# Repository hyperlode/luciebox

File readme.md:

# About
A busy box is the official word for a sensory exploratory platform for babies. 
This project was made as a birth day gift for Lucie Ameije 2019-04
Turns out, it's as interesting to adults as it is to babies. 
95% ignores abandos the box after five minutes. 5% gets hooked for days. 

Made by Uncle Sensory Overlode.
www.ameije.com

PCB and code:
https://github.com/hyperlode/luciebox

Manual:
https://docs.google.com/document/d/10EQDtFDWs3Xm5eaC9KIhdYMh6ftuR9I12zDFt4Ep7Ls/edit?usp=sharing

# Upload
- Open the arduino IDE
- Open the "luciebox" folder in the IDE
- Compile and upload should go smoothly.
- (alternatively Platformio for VS-code can be used)

# Versions
- F301: 2021-03-19: Version uploaded before sending boxes home
- F302: 2021-04-20 For the v3 startburst pcb. 
-F303: 2021-04-21: Small bugfixes, easier debug of selector dial in settings app . 
-F306: 2021-10-15: Improve user experience. Dream mode app better suited for toddlers.

# Manual
- A manual is in the "documentation folder"
- The most up to date manual is a google docs. Online at https://docs.google.com/document/d/1WturQFRmZjFw0ZYRagNDqMO8tlJvhG8SyK8Gmxv2Aj4/edit#

# Motto
- There are no bugs, only features.  Or: every bug is a feature.  (it doesn't matter if things work or not).

# Making off:
- pcbs ordered 20191112   jlc pcb (jlcpcb.com) 10 pieces for about 30cad.
- Invoice No：2818290A20191113144921
- Invoice Date：13/11/2019
- Batch No：W201911131447210

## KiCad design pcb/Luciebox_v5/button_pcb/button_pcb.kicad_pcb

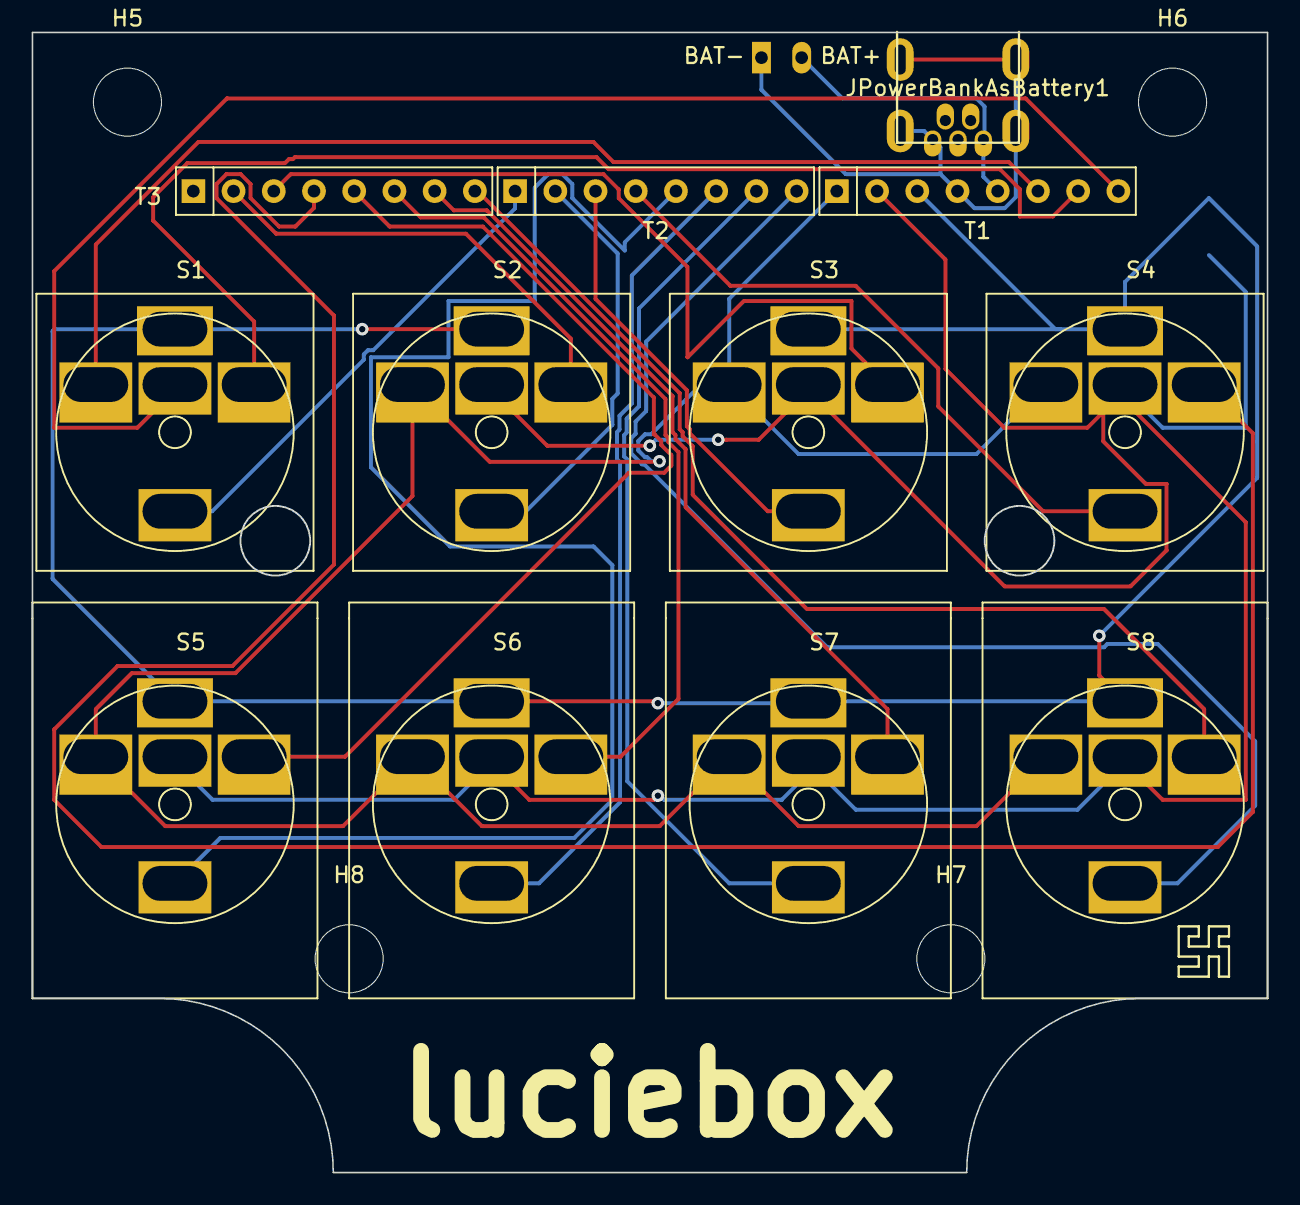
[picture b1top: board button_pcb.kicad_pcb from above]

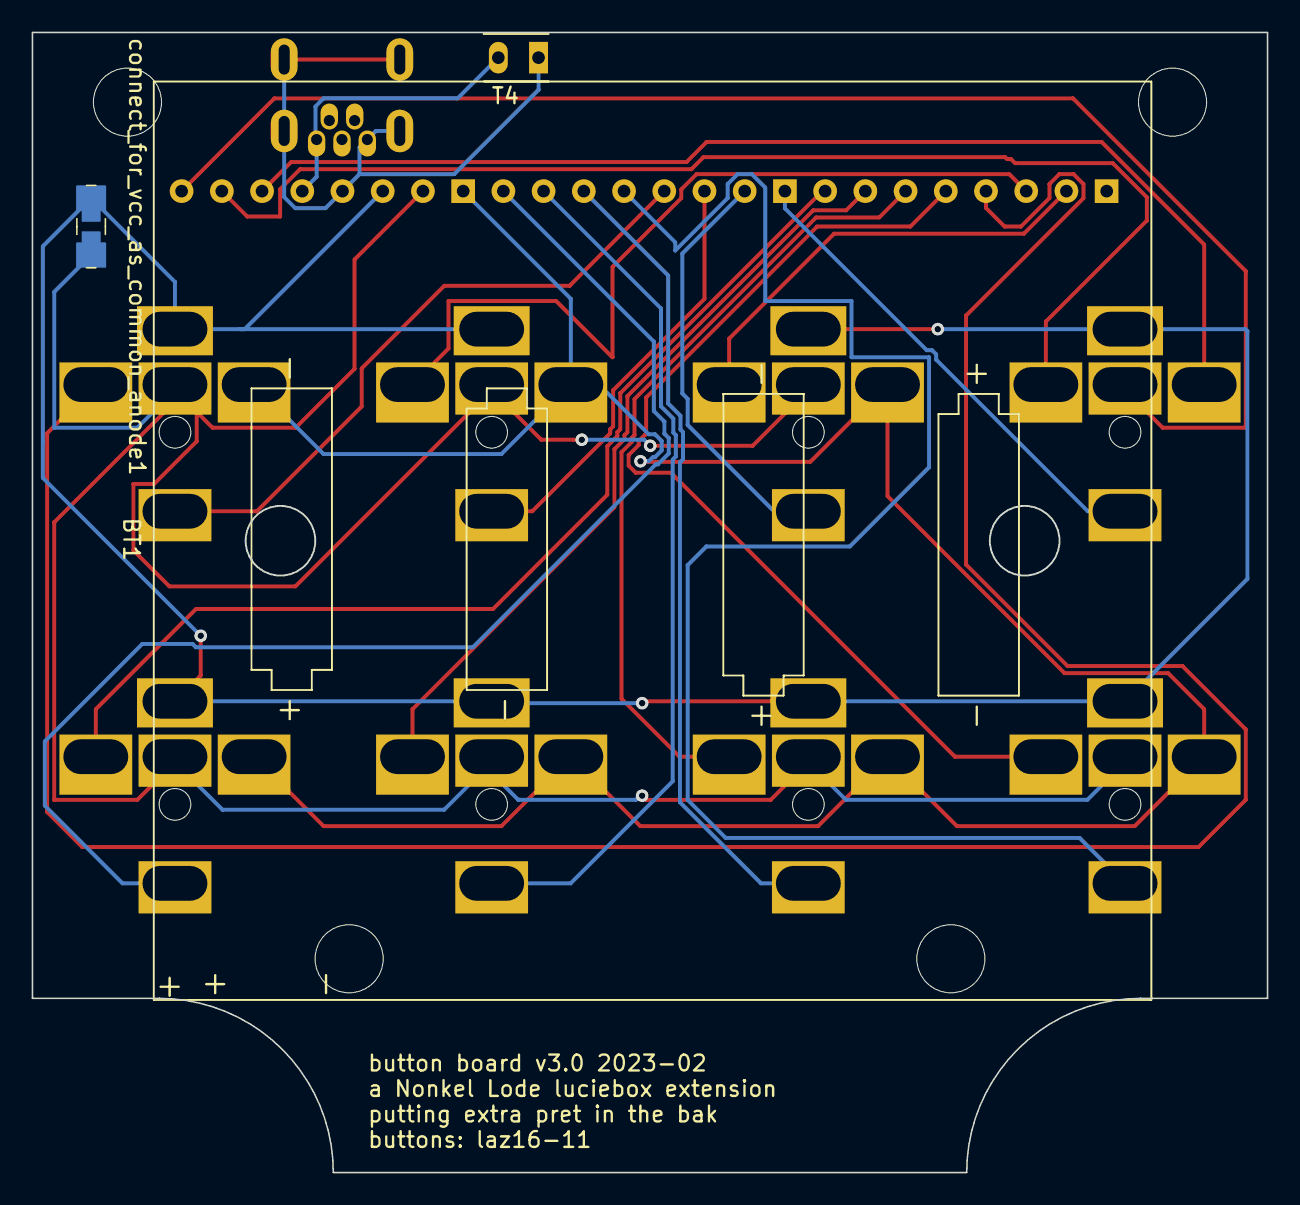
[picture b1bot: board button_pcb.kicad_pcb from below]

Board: 2 copper layers, 78.0 x 72.0 mm, 19 parts (3 on the bottom side), 23 nets.

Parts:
BT1: 4xAA_Battery_holder; BatteryHolder_4xAA
H5, H6, H7, H8: MountingHole; MountingHole_4.3mm_M4
JPowerBankAsBattery1: USB_B_Mini; usb_mini_Molex-0548190519
S1, S2, S3, S4: button_laz16-11; button_square_17.5x17.5mm_big_holes
S5, S6, S7, S8: button_laz16-11; button_LAZ16-11_big_holes
T1, T2, T3: terminal_8x1; Terminal_8x1_100mil
T4: terminal_2x1; Terminal_2x1_100mil
connect_for_vcc_as_common_anode1: R_Small; 1206_0805

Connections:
/common Anode: S1.4 (LED_+), S2.4 (LED_+), S3.4 (LED_+), S4.4 (LED_+), S5.4 (LED_+), S6.4 (LED_+), S7.4 (LED_+), S8.4 (LED_+), T1.3, connect_for_vcc_as_common_anode1.2
GND: S2.2 (NC), S3.2 (NC), S4.2 (NC), S5.2 (NC), S6.2 (NC), S7.2 (NC), S8.2 (NC), T1.1
unnamed: JPowerBankAsBattery1.5 (VBUS), T1.5, T4.2
unnamed: JPowerBankAsBattery1.1 (GND), JPowerBankAsBattery1.6 (Shield), T1.4, T4.1
unnamed: S1.1 (NO), T1.8
unnamed: S1.2 (NC), T1.6
unnamed: S1.3 (C), T1.7
unnamed: S1.5 (LED_-), T2.1
unnamed: S2.3 (C), T3.2
unnamed: S2.5 (LED_-), T2.2
unnamed: S3.3 (C), T3.3
unnamed: S3.5 (LED_-), T2.3
unnamed: S4.3 (C), T3.4
unnamed: S4.5 (LED_-), T2.4
unnamed: S5.3 (C), T3.5
unnamed: S5.5 (LED_-), T2.5
unnamed: S6.3 (C), T3.6
unnamed: S6.5 (LED_-), T2.6
unnamed: S7.3 (C), T3.7
unnamed: S7.5 (LED_-), T2.7
unnamed: S8.3 (C), T3.8
unnamed: S8.5 (LED_-), T2.8
VCC: S2.1 (NO), S3.1 (NO), S4.1 (NO), S5.1 (NO), S6.1 (NO), S7.1 (NO), S8.1 (NO), T1.2, connect_for_vcc_as_common_anode1.1

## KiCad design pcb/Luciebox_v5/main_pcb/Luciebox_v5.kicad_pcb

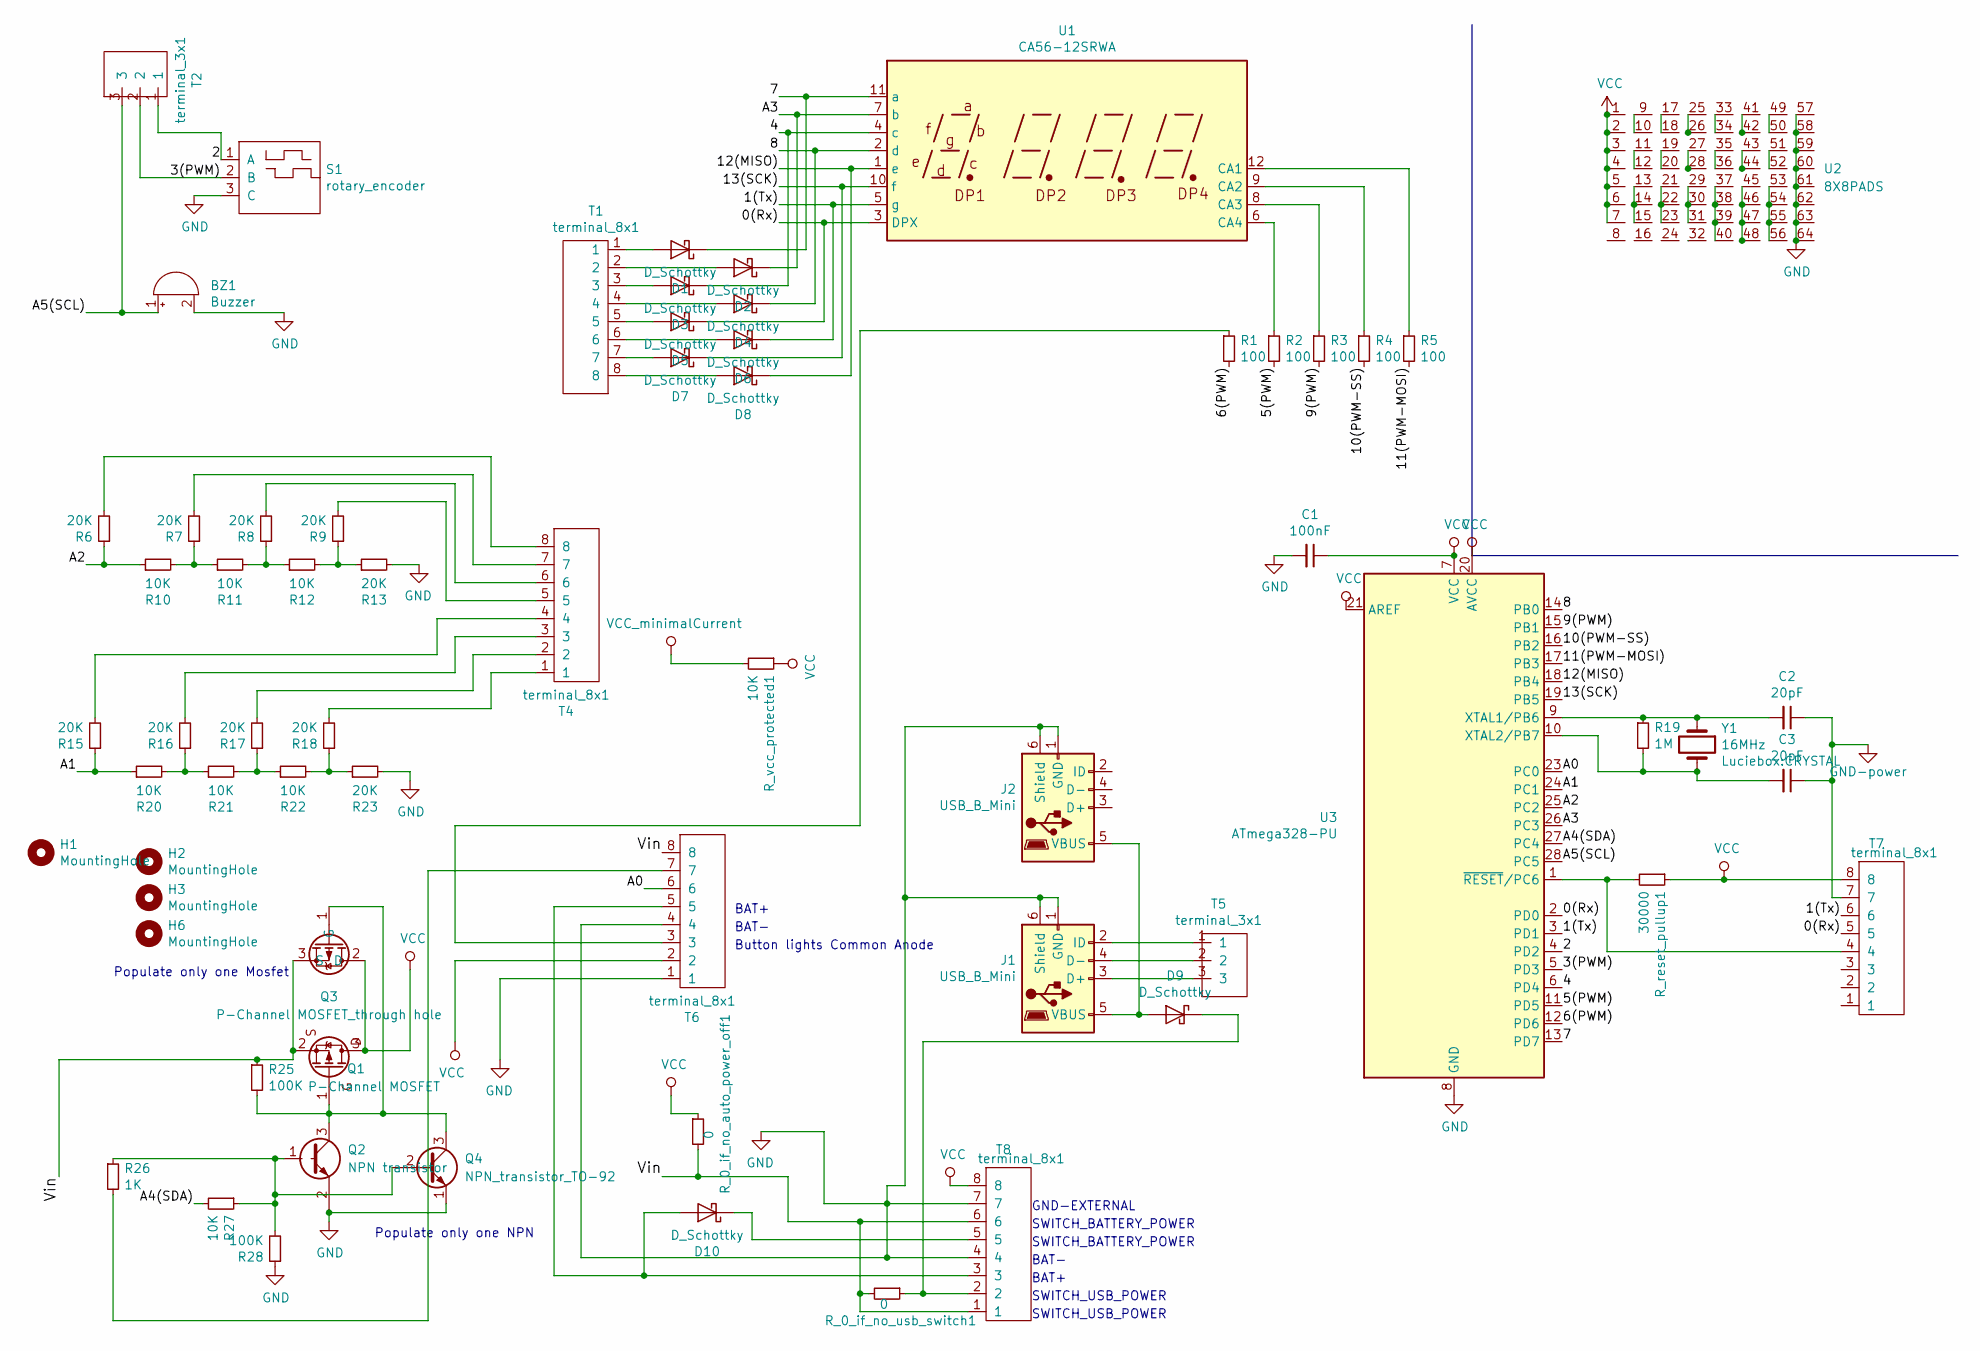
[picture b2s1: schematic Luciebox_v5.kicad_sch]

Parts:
BZ1: Buzzer; buzzer
C1: 100nF; 0603_1608Metric
C2, C3: 20pF; 0603_1608Metric
D1, D2, D3, D4, D5, D6, D7, D8, D9, D10: D_Schottky; D_SMA
H1, H2, H3, H6: MountingHole; MountingHole_4.3mm_M4
J1, J2: USB_B_Mini; usb_mini_Molex-0548190519
Q1: P-Channel MOSFET; SOT-23
Q2: NPN transistor; SOT-23
Q3: P-Channel MOSFET_through hole; TO-218-3_Vertical
Q4: NPN_transistor_TO-92; TO-92
R1, R2, R3, R4, R5: 100; 0603_1608Metric
R6, R7, R8, R9, R13, R15, R16, R17, R18, R23: 20K; 0603_1608Metric
R10, R11, R12, R20, R21, R22, R27: 10K; 0603_1608Metric
R19: 1M; 0603_1608Metric
R25, R28: 100K; 0603_1608Metric
R26: 1K; 0603_1608Metric
R_0_if_no_auto_power_off1, R_0_if_no_usb_switch1: 0; 0603_1608Metric
R_reset_pullup1: 30000; 0603_1608Metric
R_vcc_protected1: 10K; 0603_1608Metric
S1: rotary_encoder
T1, T4, T6, T7, T8: terminal_8x1; Terminal_8x1_100mil
T2, T5: terminal_3x1; Terminal_3x1_100mil
U1: CA56-12SRWA
U2: 8X8PADS; 8X8PADS_100mil
U3: ATmega328-PU; DIP-28_W7.62mm
Y1: 16MHz; CRYSTAL

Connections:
/0(Rx): D5.1 (K), T7.5, U1.3 (DPX), U3.2 (PD0)
/1(Tx): D6.1 (K), T7.6, U1.5 (g), U3.3 (PD1)
/2: S1.1 (A), T2.1, U3.4 (PD2)
/3(PWM): S1.2 (B), T2.2, U3.5 (PD3)
/4: D3.1 (K), U1.4 (c), U3.6 (PD4)
/5(PWM): R2.2, U3.11 (PD5)
/6(PWM): R1.2, U3.12 (PD6)
/7: D1.1 (K), U1.11 (a), U3.13 (PD7)
/8: D4.1 (K), U1.2 (d), U3.14 (PB0)
/9(PWM): R3.2, U3.15 (PB1)
/10(PWM-SS): R4.2, U3.16 (PB2)
/11(PWM-MOSI): R5.2, U3.17 (PB3)
/12(MISO): D8.1 (K), U1.1 (e), U3.18 (PB4)
/13(SCK): D7.1 (K), U1.10 (f), U3.19 (PB5)
/A0: T6.6, U3.23 (PC0)
/A1: R15.1, R20.1, U3.24 (PC1)
/A2: R6.1, R10.1, U3.25 (PC2)
/A3: D2.1 (K), U1.7 (b), U3.26 (PC3)
/A4(SDA): R27.2, U3.27 (PC4)
/A5(SCL): BZ1.1 (-), T2.3, U3.28 (PC5)
/Vin: Q1.2 (S), Q3.3 (S), R25.1, R_0_if_no_auto_power_off1.2, R_0_if_no_usb_switch1.2, T6.8, T8.1, T8.6
unnamed: C2.2, R19.1, U3.9 (XTAL1/PB6), Y1.1
unnamed: C3.2, R19.2, U3.10 (XTAL2/PB7), Y1.2
unnamed: D1.2 (A), T1.1
unnamed: D2.2 (A), T1.2
unnamed: D3.2 (A), T1.3
unnamed: D4.2 (A), T1.4
unnamed: D5.2 (A), T1.5
unnamed: D6.2 (A), T1.6
unnamed: D7.2 (A), T1.7
unnamed: D8.2 (A), T1.8
unnamed: D9.1 (K), R_0_if_no_usb_switch1.1, T8.2
unnamed: D9.2 (A), J1.5 (VBUS), J2.5 (VBUS)
unnamed: D10.1 (K), T8.5
unnamed: D10.2 (A), T6.5, T8.3
unnamed: J1.2 (ID), T5.1
unnamed: J1.3 (D+), T5.3
unnamed: J1.4 (D-), T5.2
unnamed: Q1.1 (G), Q2.3 (E), Q3.1 (G), Q4.3 (E), R25.2
unnamed: Q2.1 (C), Q4.2 (B), R26.1, R27.1, R28.2
unnamed: R1.1, T6.3
unnamed: R2.1, U1.6 (CA4)
unnamed: R3.1, U1.8 (CA3)
unnamed: R4.1, U1.9 (CA2)
unnamed: R5.1, U1.12 (CA1)
unnamed: R6.2, T4.8
unnamed: R7.2, T4.7
unnamed: R8.2, T4.6
unnamed: R9.2, T4.5
unnamed: R7.1, R10.2, R11.1
unnamed: R8.1, R11.2, R12.1
unnamed: R9.1, R12.2, R13.1
unnamed: R15.2, T4.4
unnamed: R16.1, R20.2, R21.1
unnamed: R16.2, T4.3
unnamed: R17.1, R21.2, R22.1
unnamed: R17.2, T4.2
unnamed: R18.1, R22.2, R23.1
unnamed: R18.2, T4.1
unnamed: R26.2, T6.7
unnamed: R_reset_pullup1.2, T7.4, U3.1 (~RESET/PC6)
unnamed: U2.9, U2.10
unnamed: U2.11, U2.12
unnamed: U2.13, U2.14, U2.15
unnamed: U2.17, U2.18
unnamed: U2.19, U2.20
unnamed: U2.21, U2.22, U2.23
unnamed: U2.25, U2.26
unnamed: U2.27, U2.28
unnamed: U2.29, U2.30, U2.31
unnamed: U2.33, U2.34
unnamed: U2.35, U2.36
unnamed: U2.37, U2.38, U2.39, U2.40
unnamed: U2.41, U2.42
unnamed: U2.43, U2.44
unnamed: U2.45, U2.46, U2.47, U2.48
unnamed: U2.49, U2.50
unnamed: U2.51, U2.52
unnamed: U2.53, U2.54, U2.55, U2.56
VCC: C1.1, Q1.3 (D), Q3.2 (D), R_0_if_no_auto_power_off1.1, R_reset_pullup1.1, R_vcc_protected1.1, T6.2, T7.8, T8.8, U2.1, U2.2, U2.3, U2.4, U2.5, U2.6, U2.7, U3.7 (VCC), U3.20 (AVCC), U3.21 (AREF)
VCC_minimalCurrent: R_vcc_protected1.2

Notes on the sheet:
GND-EXTERNAL
BAT-
Populate only one NPN
BAT+
SWITCH_BATTERY_POWER
SWITCH_USB_POWER
Populate only one Mosfet
Button lights Common Anode

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
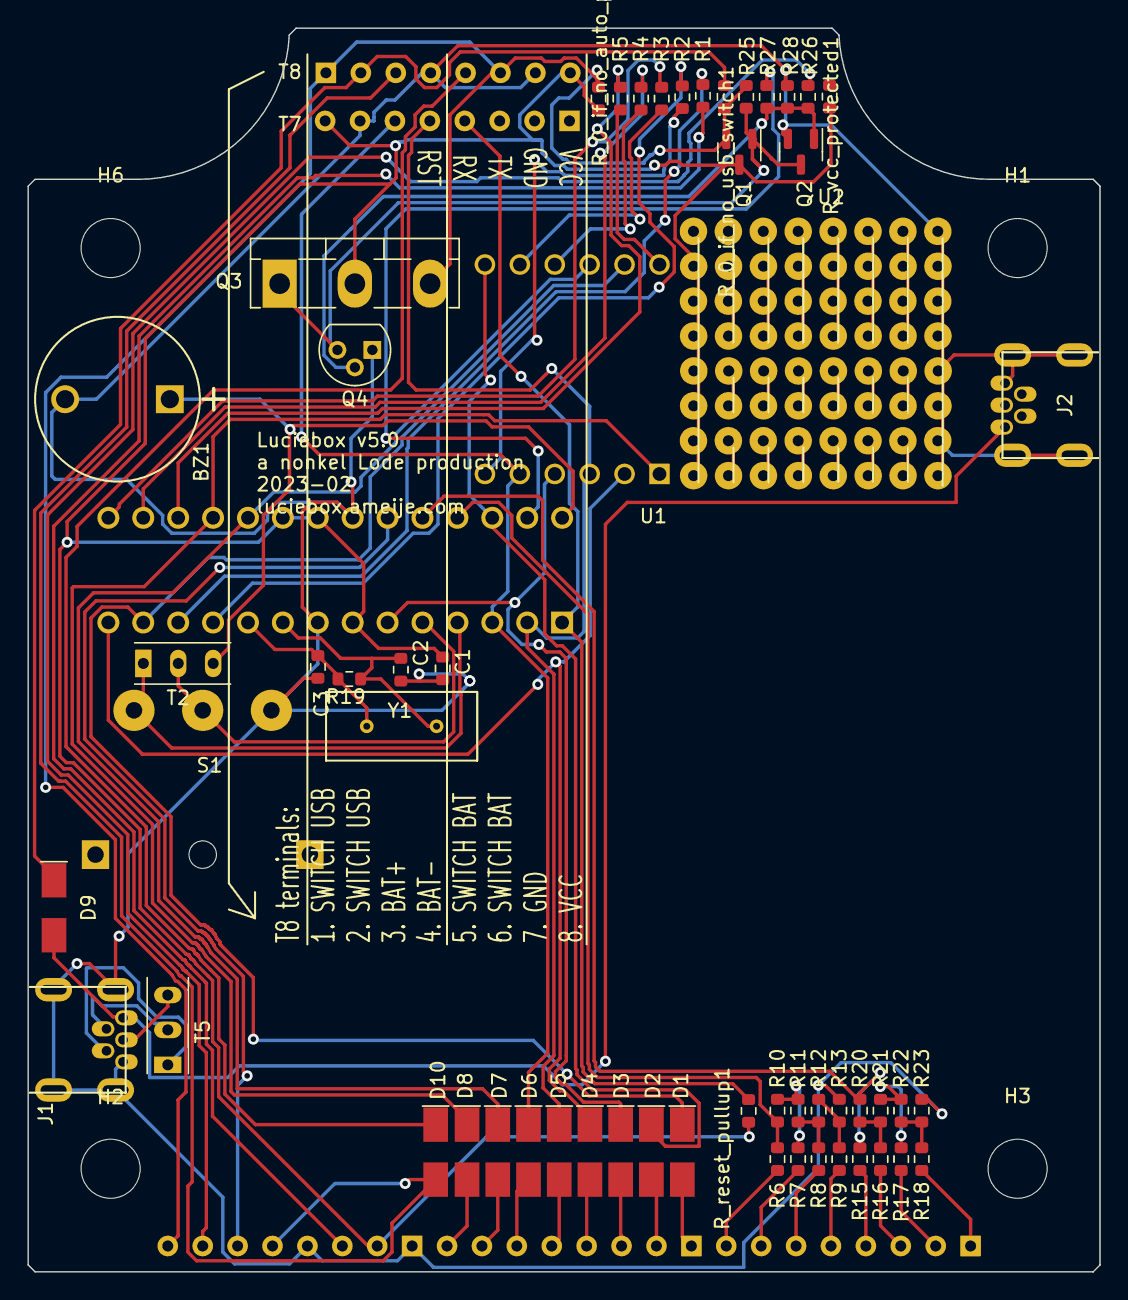
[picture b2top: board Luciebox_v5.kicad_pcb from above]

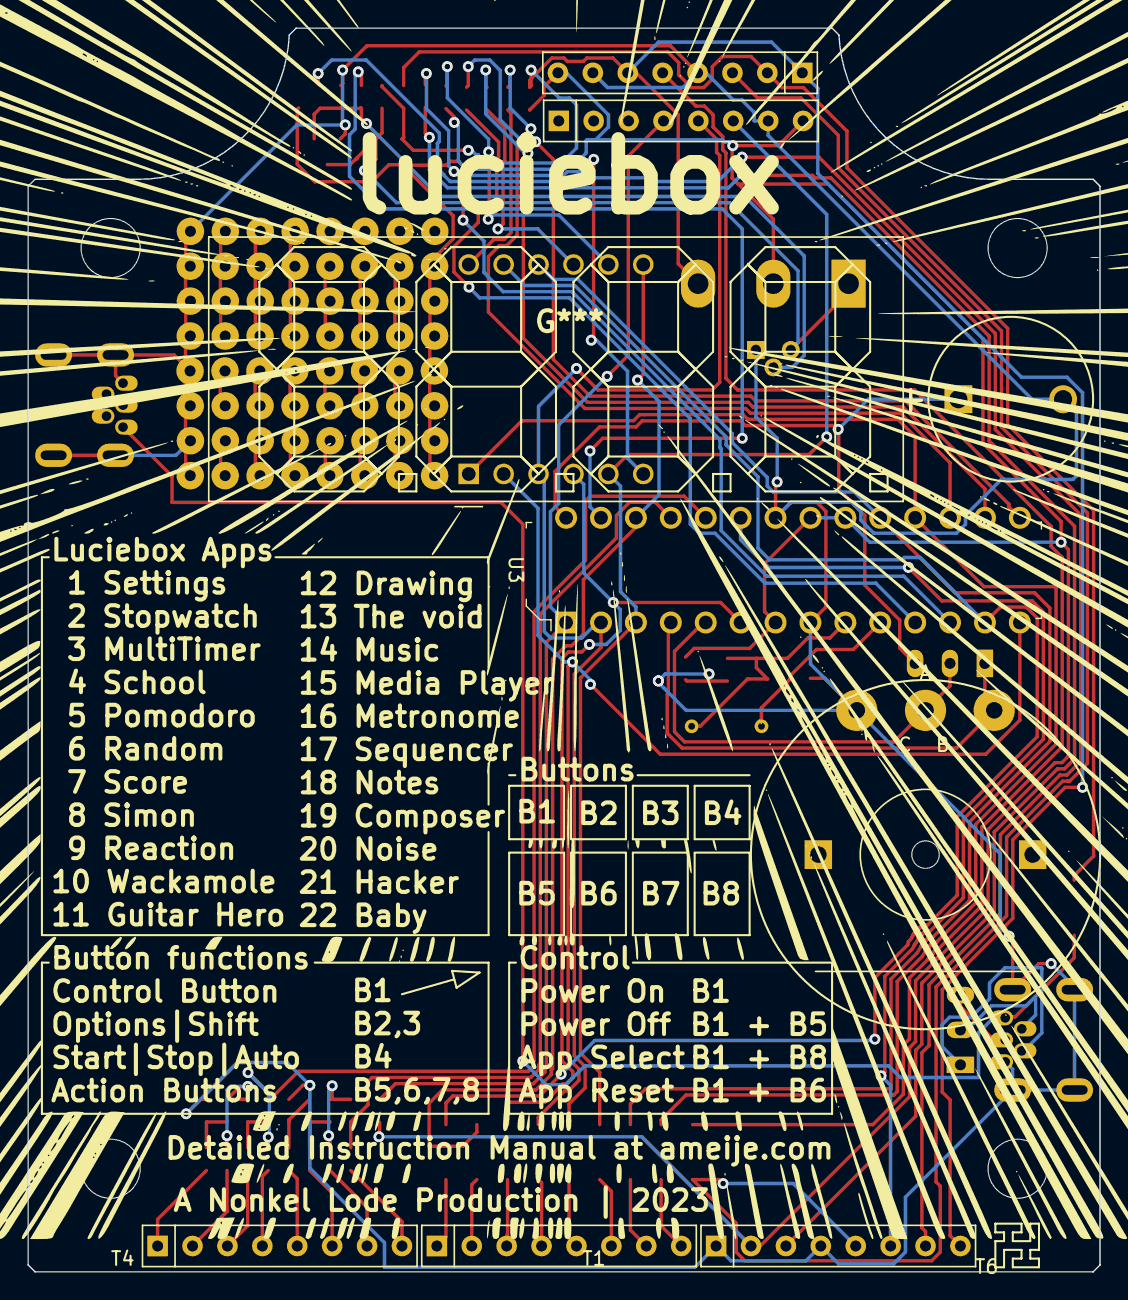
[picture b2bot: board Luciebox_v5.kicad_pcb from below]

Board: 2 copper layers, 78.0 x 90.5 mm, 66 parts (9 on the bottom side), 81 nets.

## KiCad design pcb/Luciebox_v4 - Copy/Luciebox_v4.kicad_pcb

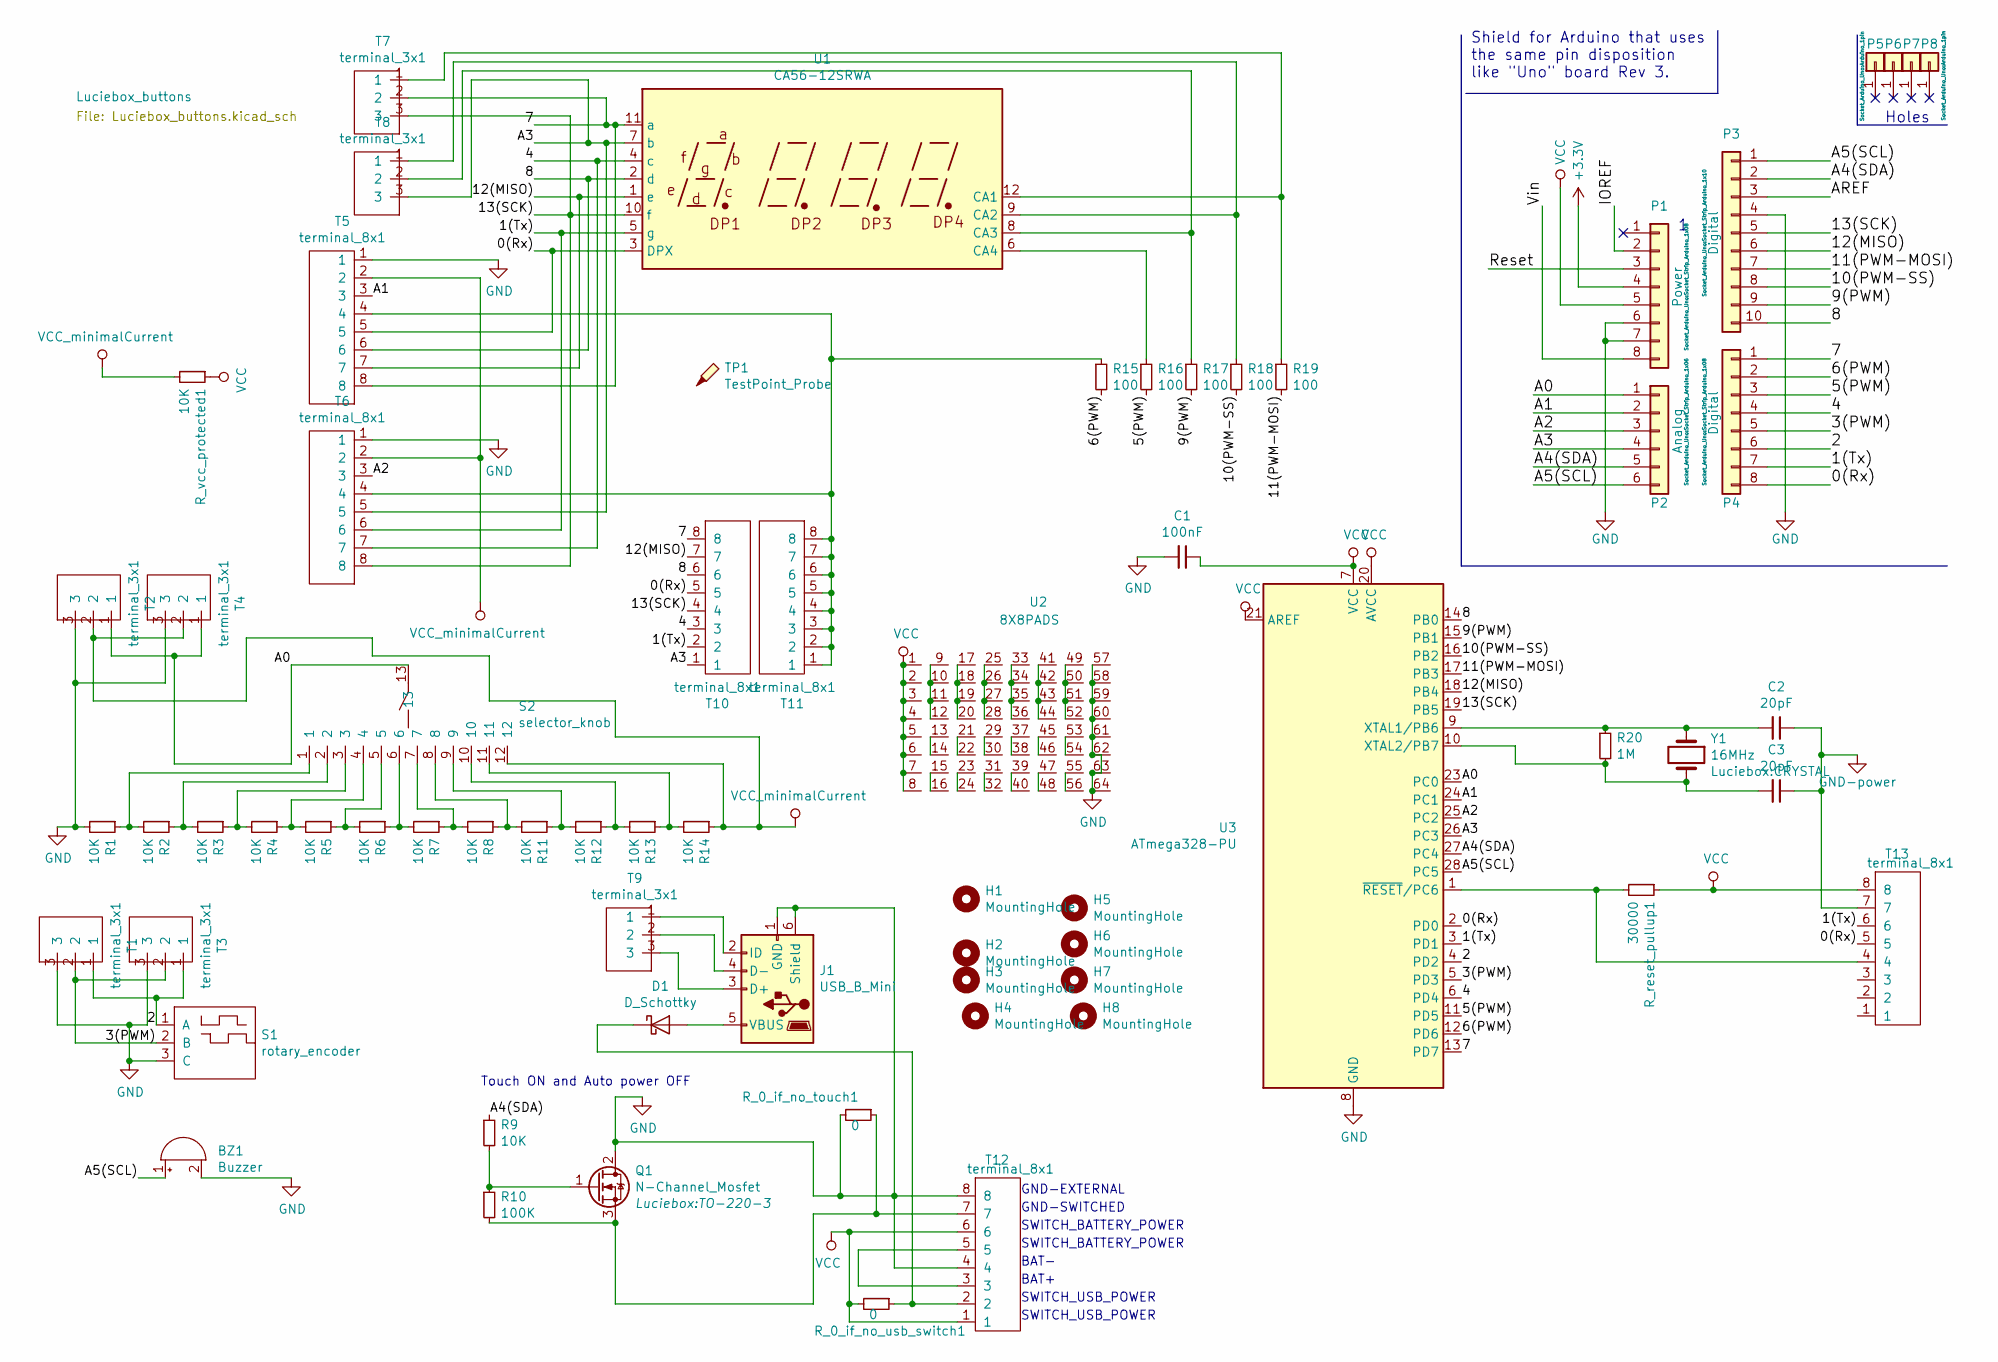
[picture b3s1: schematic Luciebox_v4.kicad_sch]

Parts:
BZ1: Buzzer; buzzer
C1: 100nF; 0805
C2, C3: 20pF; 0805
D1: D_Schottky; smd_throughhole_2_pins
H1, H2, H3, H4, H5, H6, H7, H8: MountingHole; MountingHole_4.3mm_M4
J1: USB_B_Mini; usb_mini_Molex-0548190519
P1: Power; Socket_Strip_Arduino_1x08
P2: Analog; Socket_Strip_Arduino_1x06
P3: Digital; Socket_Strip_Arduino_1x10
P4: Digital; Socket_Strip_Arduino_1x08
P5, P6, P7, P8: CONN_01X01; Arduino_1pin
Q1: N-Channel_Mosfet; TO-220-3
R1, R2, R3, R4, R5, R6, R7, R8, R9, R11, R12, R13, R14: 10K; 1206_0805
R10: 100K; 1206_0805
R15, R16, R17, R18, R19: 100; 1206_0805
R20: 1M; 1206_0805
R_0_if_no_touch1, R_0_if_no_usb_switch1: 0; 1206_0805
R_reset_pullup1: 30000; 1206_0805
R_vcc_protected1: 10K; 1206_0805
S1: rotary_encoder
S2: selector_knob; Rotary_Switch
T1, T2, T3, T4, T7, T8, T9: terminal_3x1; Terminal_3x1_100mil
T5, T6, T10, T11, T12, T13: terminal_8x1; Terminal_8x1_100mil
TP1: TestPoint_Probe
U1: CA56-12SRWA
U2: 8X8PADS; 64_PADS_100mil
U3: ATmega328-PU; DIP-28_W7.62mm
Y1: 16MHz; CRYSTAL

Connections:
+3V3: P1.4
/0(Rx): P4.8, T5.5, T10.5, T13.5, U1.3 (DPX), U3.2 (PD0)
/1(Tx): P4.7, T6.6, T10.2, T13.6, U1.5 (g), U3.3 (PD1)
/2: P4.6, S1.1 (A), T1.1, T3.1, U3.4 (PD2)
/3(PWM): P4.5, S1.2 (B), T1.2, T3.2, U3.5 (PD3)
/4: P4.4, T6.7, T10.3, U1.4 (c), U3.6 (PD4)
/5(PWM): P4.3, R16.2, U3.11 (PD5)
/6(PWM): P4.2, R15.2, U3.12 (PD6)
/7: P4.1, T5.8, T7.2, T10.8, U1.11 (a), U3.13 (PD7)
/8: P3.10, T5.6, T10.6, U1.2 (d), U3.14 (PB0)
/9(PWM): P3.9, R17.2, U3.15 (PB1)
/10(PWM-SS): P3.8, R18.2, U3.16 (PB2)
/11(PWM-MOSI): P3.7, R19.2, U3.17 (PB3)
/12(MISO): P3.6, T5.7, T10.7, U1.1 (e), U3.18 (PB4)
/13(SCK): P3.5, T6.8, T7.3, T10.4, U1.10 (f), U3.19 (PB5)
/A0: P2.1, S2.13, T2.1, T4.1, U3.23 (PC0)
/A1: P2.2, T5.3, U3.24 (PC1)
/A2: P2.3, T6.3, U3.25 (PC2)
/A3: P2.4, T6.5, T8.3, T10.1, U1.7 (b), U3.26 (PC3)
/A4(SDA): P2.5, P3.2, R9.1, U3.27 (PC4)
/A5(SCL): BZ1.1 (-), P2.6, P3.1, U3.28 (PC5)
/AREF: P3.3
/IOREF: P1.2
/Reset: P1.3
/Vin: P1.8
unnamed: C2.2, R20.1, U3.9 (XTAL1/PB6), Y1.1
unnamed: C3.2, R20.2, U3.10 (XTAL2/PB7), Y1.2
unnamed: D1.1 (K), R_0_if_no_usb_switch1.1, T12.2
unnamed: D1.2 (A), J1.5 (VBUS)
unnamed: J1.2 (ID), T9.1
unnamed: J1.3 (D+), T9.3
unnamed: J1.4 (D-), T9.2
unnamed: Q1.1 (G), R9.2, R10.1
unnamed: Q1.3 (S), R10.2, R_0_if_no_touch1.1, T12.7
unnamed: R1.1, R2.2, S2.1
unnamed: R2.1, R3.2, S2.2
unnamed: R3.1, R4.2, S2.3
unnamed: R4.1, R5.2, S2.4
unnamed: R5.1, R6.2, S2.5
unnamed: R6.1, R7.2, S2.6
unnamed: R7.1, R8.2, S2.7
unnamed: R11.1, R12.2, S2.9
unnamed: R8.1, R11.2, S2.8
unnamed: R12.1, R13.2, S2.10
unnamed: R13.1, R14.2, S2.11
unnamed: R15.1, T5.4, T6.4, T11.1, T11.2, T11.3, T11.4, T11.5, T11.6, T11.7, T11.8
unnamed: R16.1, U1.6 (CA4)
unnamed: R17.1, T8.2, U1.8 (CA3)
unnamed: R18.1, T8.1, U1.9 (CA2)
unnamed: R19.1, T7.1, U1.12 (CA1)
unnamed: R_reset_pullup1.2, T13.4, U3.1 (~RESET/PC6)
unnamed: T12.3, T12.5
unnamed: U2.9, U2.10, U2.11, U2.12
unnamed: U2.13, U2.14
unnamed: U2.15, U2.16
unnamed: U2.17, U2.18, U2.19, U2.20
unnamed: U2.21, U2.22
unnamed: U2.23, U2.24
unnamed: U2.25, U2.26, U2.27, U2.28
unnamed: U2.29, U2.30
unnamed: U2.31, U2.32
unnamed: U2.33, U2.34, U2.35, U2.36
unnamed: U2.37, U2.38
unnamed: U2.39, U2.40
unnamed: U2.41, U2.42, U2.43, U2.44
unnamed: U2.45, U2.46
unnamed: U2.47, U2.48
unnamed: U2.49, U2.50, U2.51, U2.52
unnamed: U2.53, U2.54
unnamed: U2.55, U2.56
VCC: C1.1, P1.5, R_0_if_no_usb_switch1.2, R_reset_pullup1.1, R_vcc_protected1.1, T12.1, T12.6, T13.8, U2.1, U2.2, U2.3, U2.4, U2.5, U2.6, U2.7, U2.8, U3.7 (VCC), U3.20 (AVCC), U3.21 (AREF)
VCC_minimalCurrent: R14.1, R_vcc_protected1.2, S2.12, T2.2, T4.2, T5.2, T6.2

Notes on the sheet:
Holes
GND-EXTERNAL
BAT-
Touch ON and Auto power OFF
Shield for Arduino that uses the same pin disposition like "Uno" board Rev 3.
GND-SWITCHED
BAT+
SWITCH_BATTERY_POWER
SWITCH_USB_POWER

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
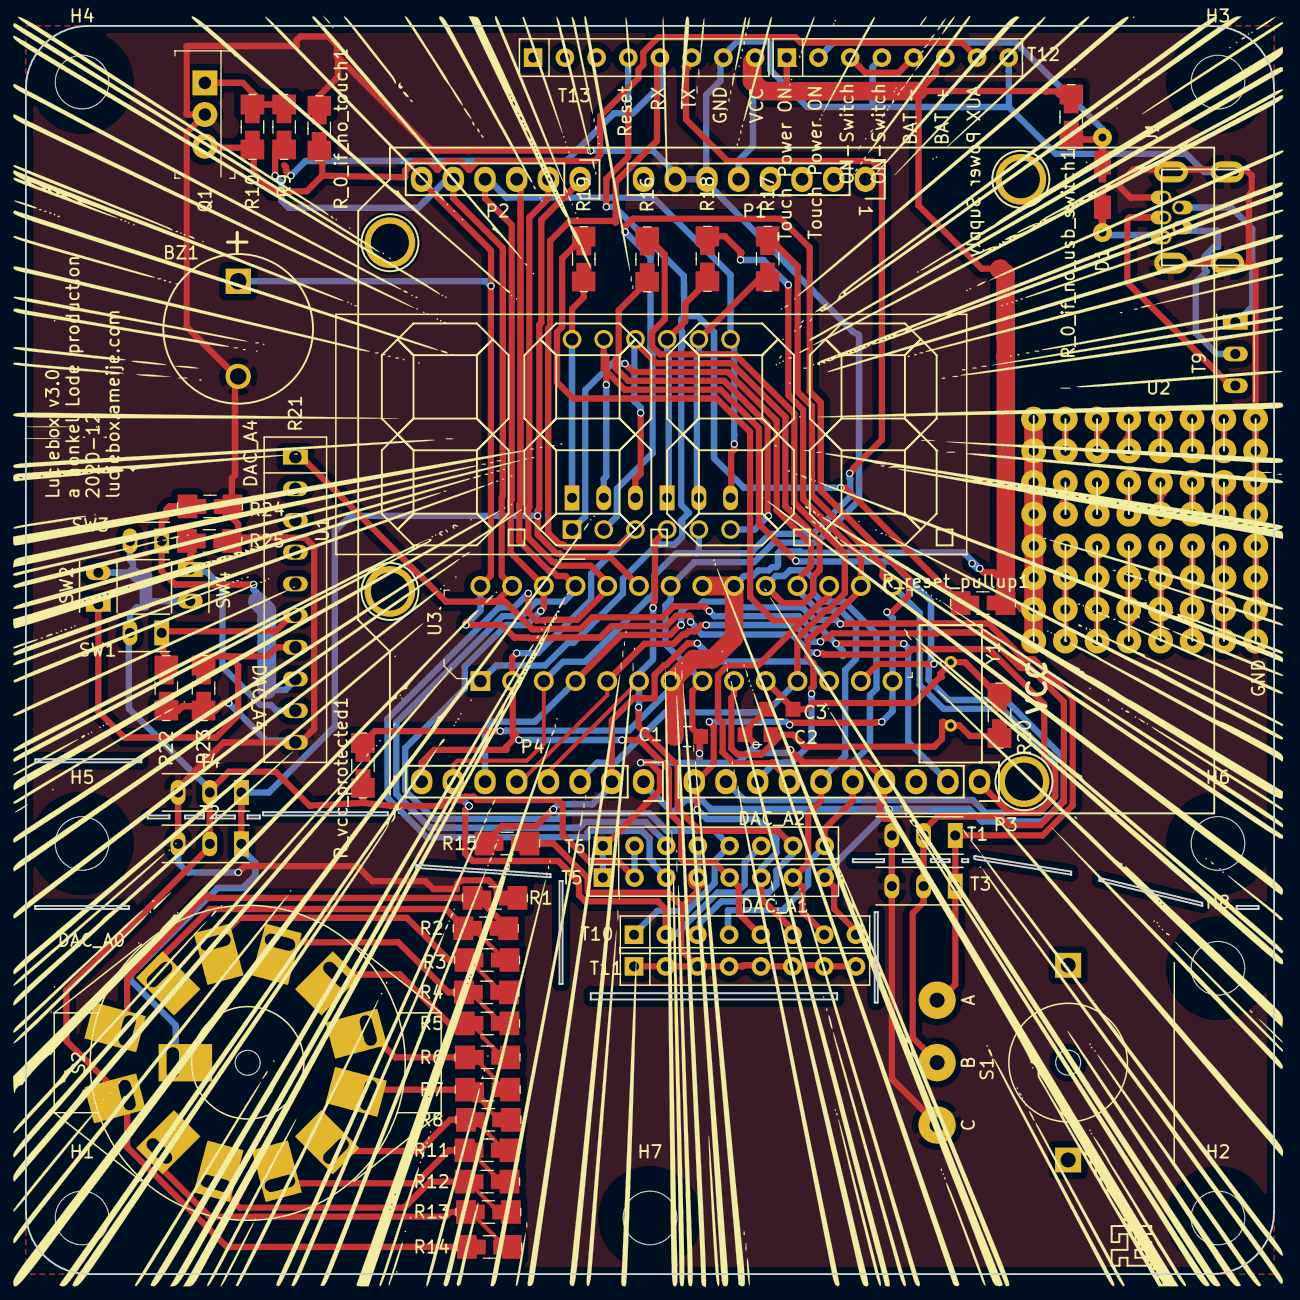
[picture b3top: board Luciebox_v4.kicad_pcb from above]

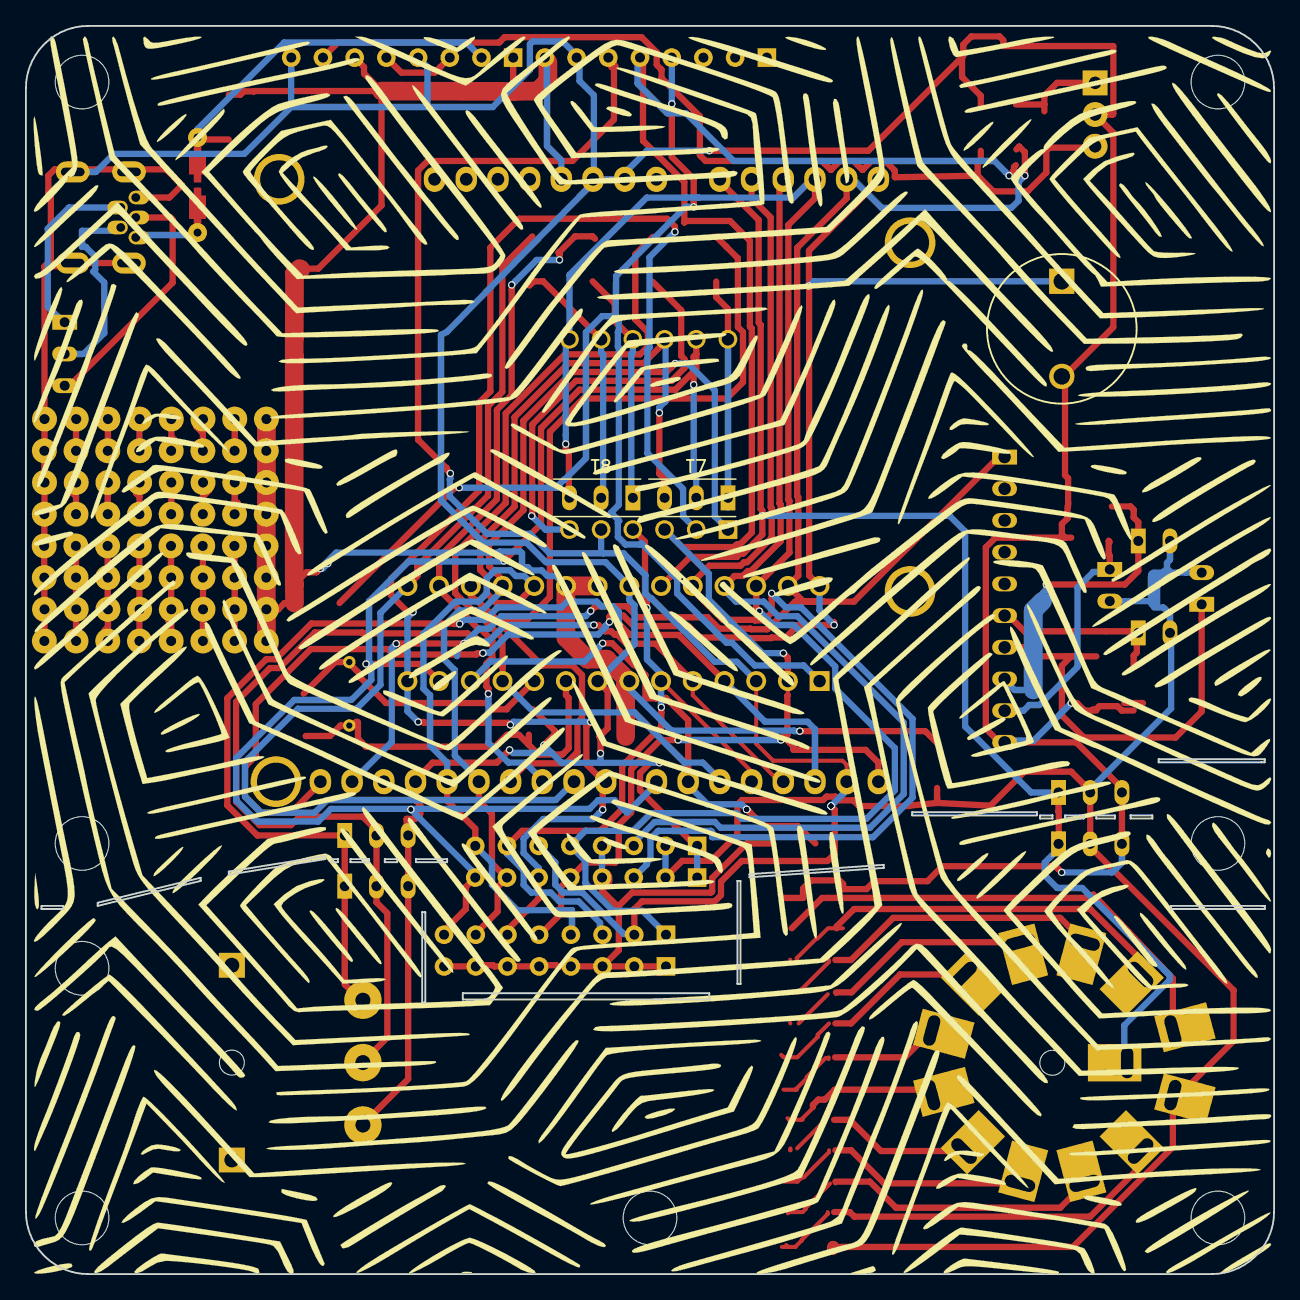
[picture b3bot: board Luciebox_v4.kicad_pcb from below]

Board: 2 copper layers, 100.0 x 100.0 mm, 75 parts (2 on the bottom side), 68 nets.

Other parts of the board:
R21: DAC_R-2R; SIP-10
R22, R23, R24, R25: R_Small; 1206_0805
SW1, SW2, SW3, SW4: Switch_tilt; Terminal_2x1_100mil
